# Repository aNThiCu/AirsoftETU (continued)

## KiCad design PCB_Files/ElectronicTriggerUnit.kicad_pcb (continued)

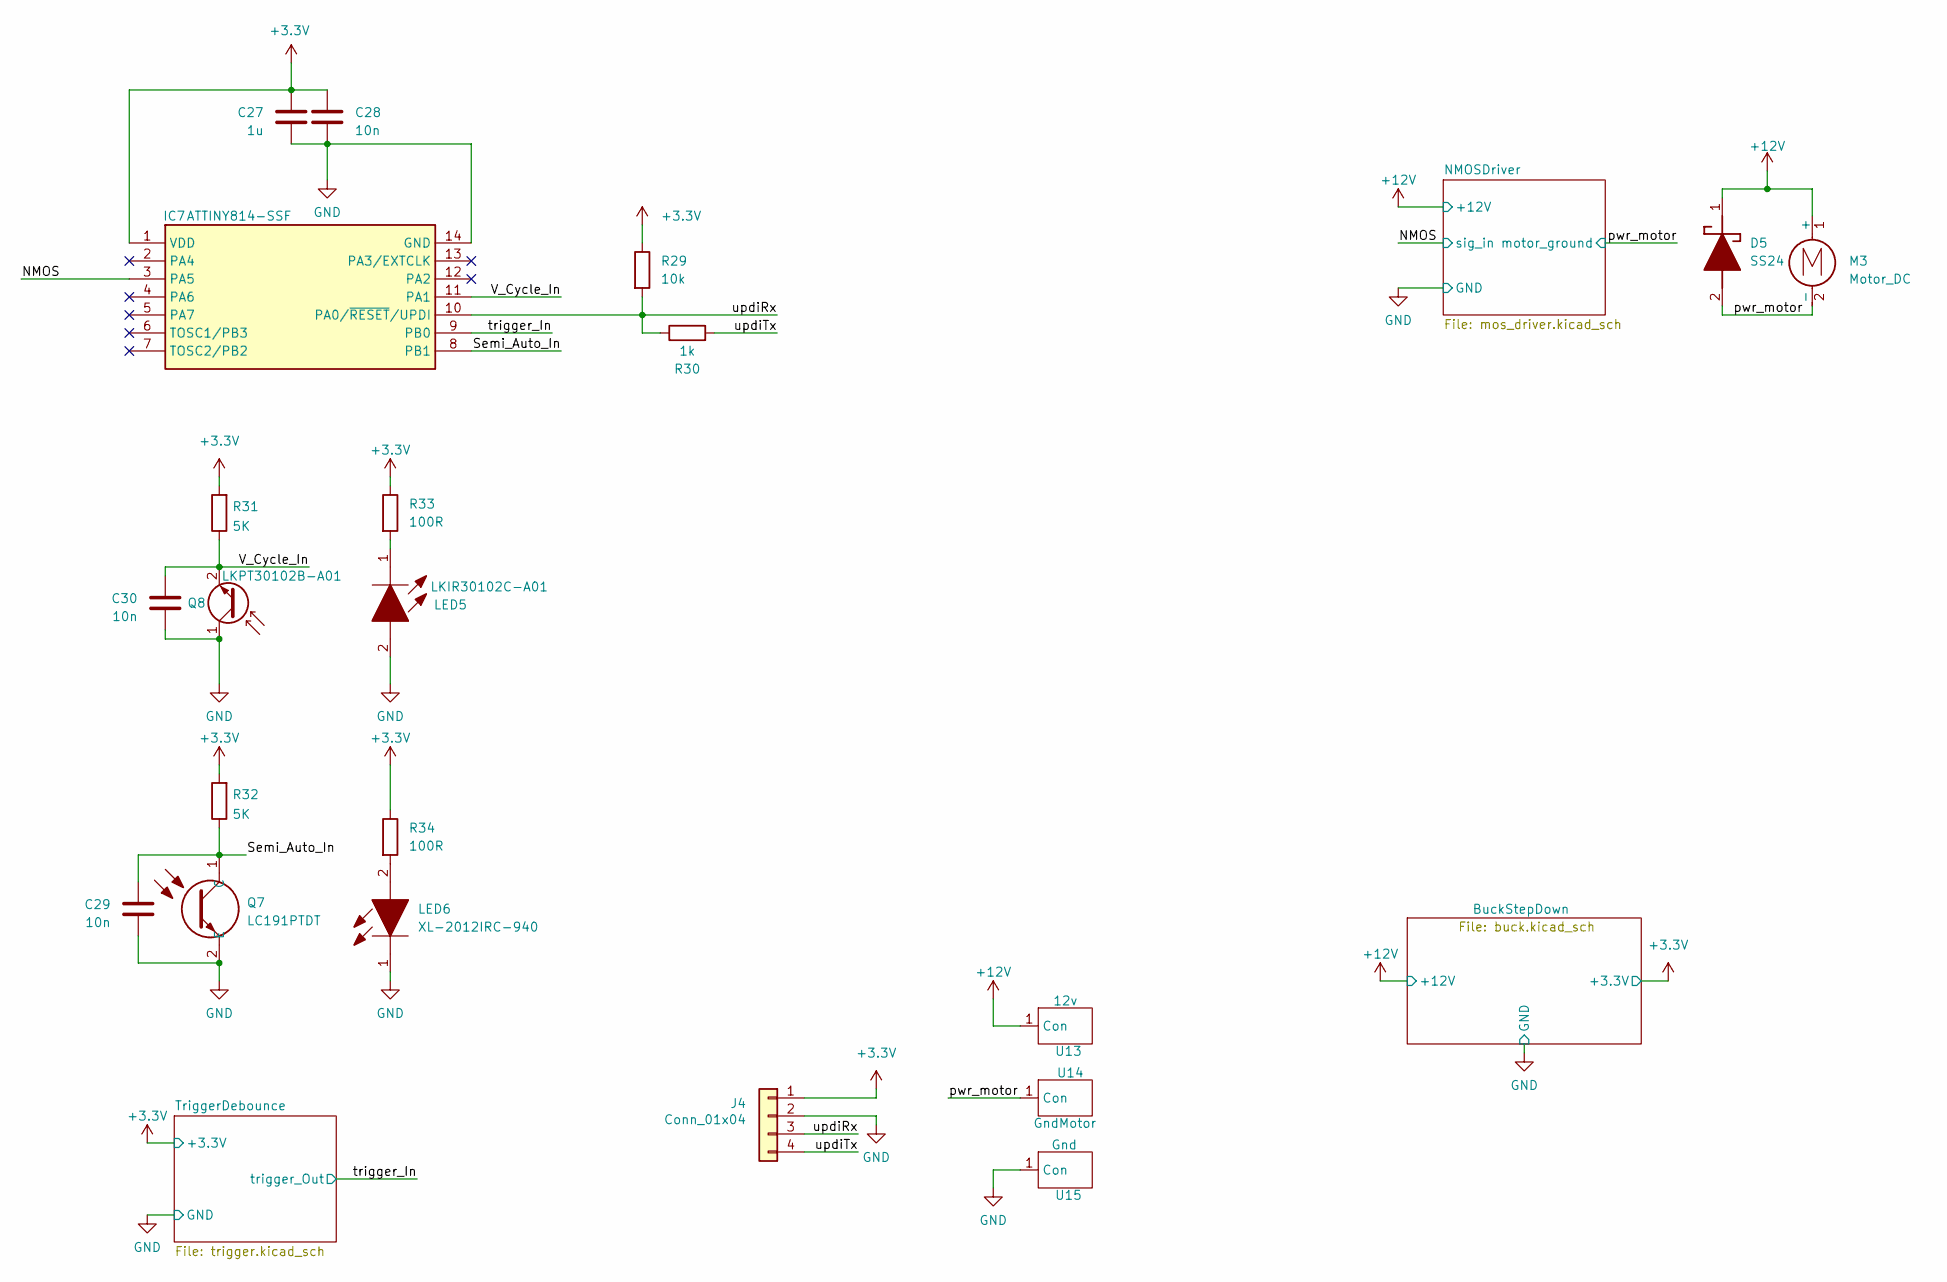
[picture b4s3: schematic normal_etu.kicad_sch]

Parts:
C27: 1u; C_0603_1608Metric
C28, C29, C30: 10n; C_0603_1608Metric
D5: SS24; DIOM5436X247N; Mouser Part Number 821-SS24
IC7: ATTINY814-SSF; SOIC127P600X175-14N; Mouser Part Number 579-ATTINY814-SSF
J4: Conn_01x04; PinHeader_1x04_P2.54mm_Vertical
LED5: LKIR30102C-A01; APA3010P3C; Mouser Part Number 755-CSL1501RW1
LED6: XL-2012IRC-940; LEDC2012X105N; Mouser Part Number 604-APTD2012SF4C
M3: Motor_DC
Q7: LC191PTDT; AP1608P1CP22; Mouser Part Number 604-AP1608P1C-P22
Q8: LKPT30102B-A01; APA3010P3C
R29: 10k; R_0603_1608Metric
R30: 1k; R_0603_1608Metric
R31, R32: 5K; R_0603_1608Metric
R33, R34: 100R; R_0603_1608Metric
U13: 12v; Copper_Pad
U14: GndMotor; Copper_Pad
U15: Gnd; Copper_Pad

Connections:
+3.3V: C27.1, C28.1, IC7.1 (VDD), J4.1, R29.1, R31.2, R32.2, R33.1, R34.1; also elsewhere on the board
+12V: D5.1 (K), M3.1 (+), U13.1 (Con); also elsewhere on the board
/NormalEtu/NMOS: IC7.3 (PA5); also elsewhere on the board
/NormalEtu/Semi_Auto_In: C29.1, IC7.8 (PB1), Q7.1 (C), R32.1
/NormalEtu/V_Cycle_In: C30.1, IC7.11 (PA1), Q8.2 (E), R31.1
/NormalEtu/pwr_motor: D5.2 (A), M3.2 (-), U14.1 (Con); also elsewhere on the board
/NormalEtu/trigger_In: IC7.9 (PB0); also elsewhere on the board
/NormalEtu/updiRx: IC7.10 (PA0/~RESET/UPDI), J4.3, R29.2, R30.1
/NormalEtu/updiTx: J4.4, R30.2
GND: C27.2, C28.2, C29.2, C30.2, IC7.14 (GND), J4.2, LED5.2, LED6.1, Q7.2 (E), Q8.1 (C), U15.1 (Con); also elsewhere on the board
unnamed: LED5.1, R33.2
unnamed: LED6.2, R34.2

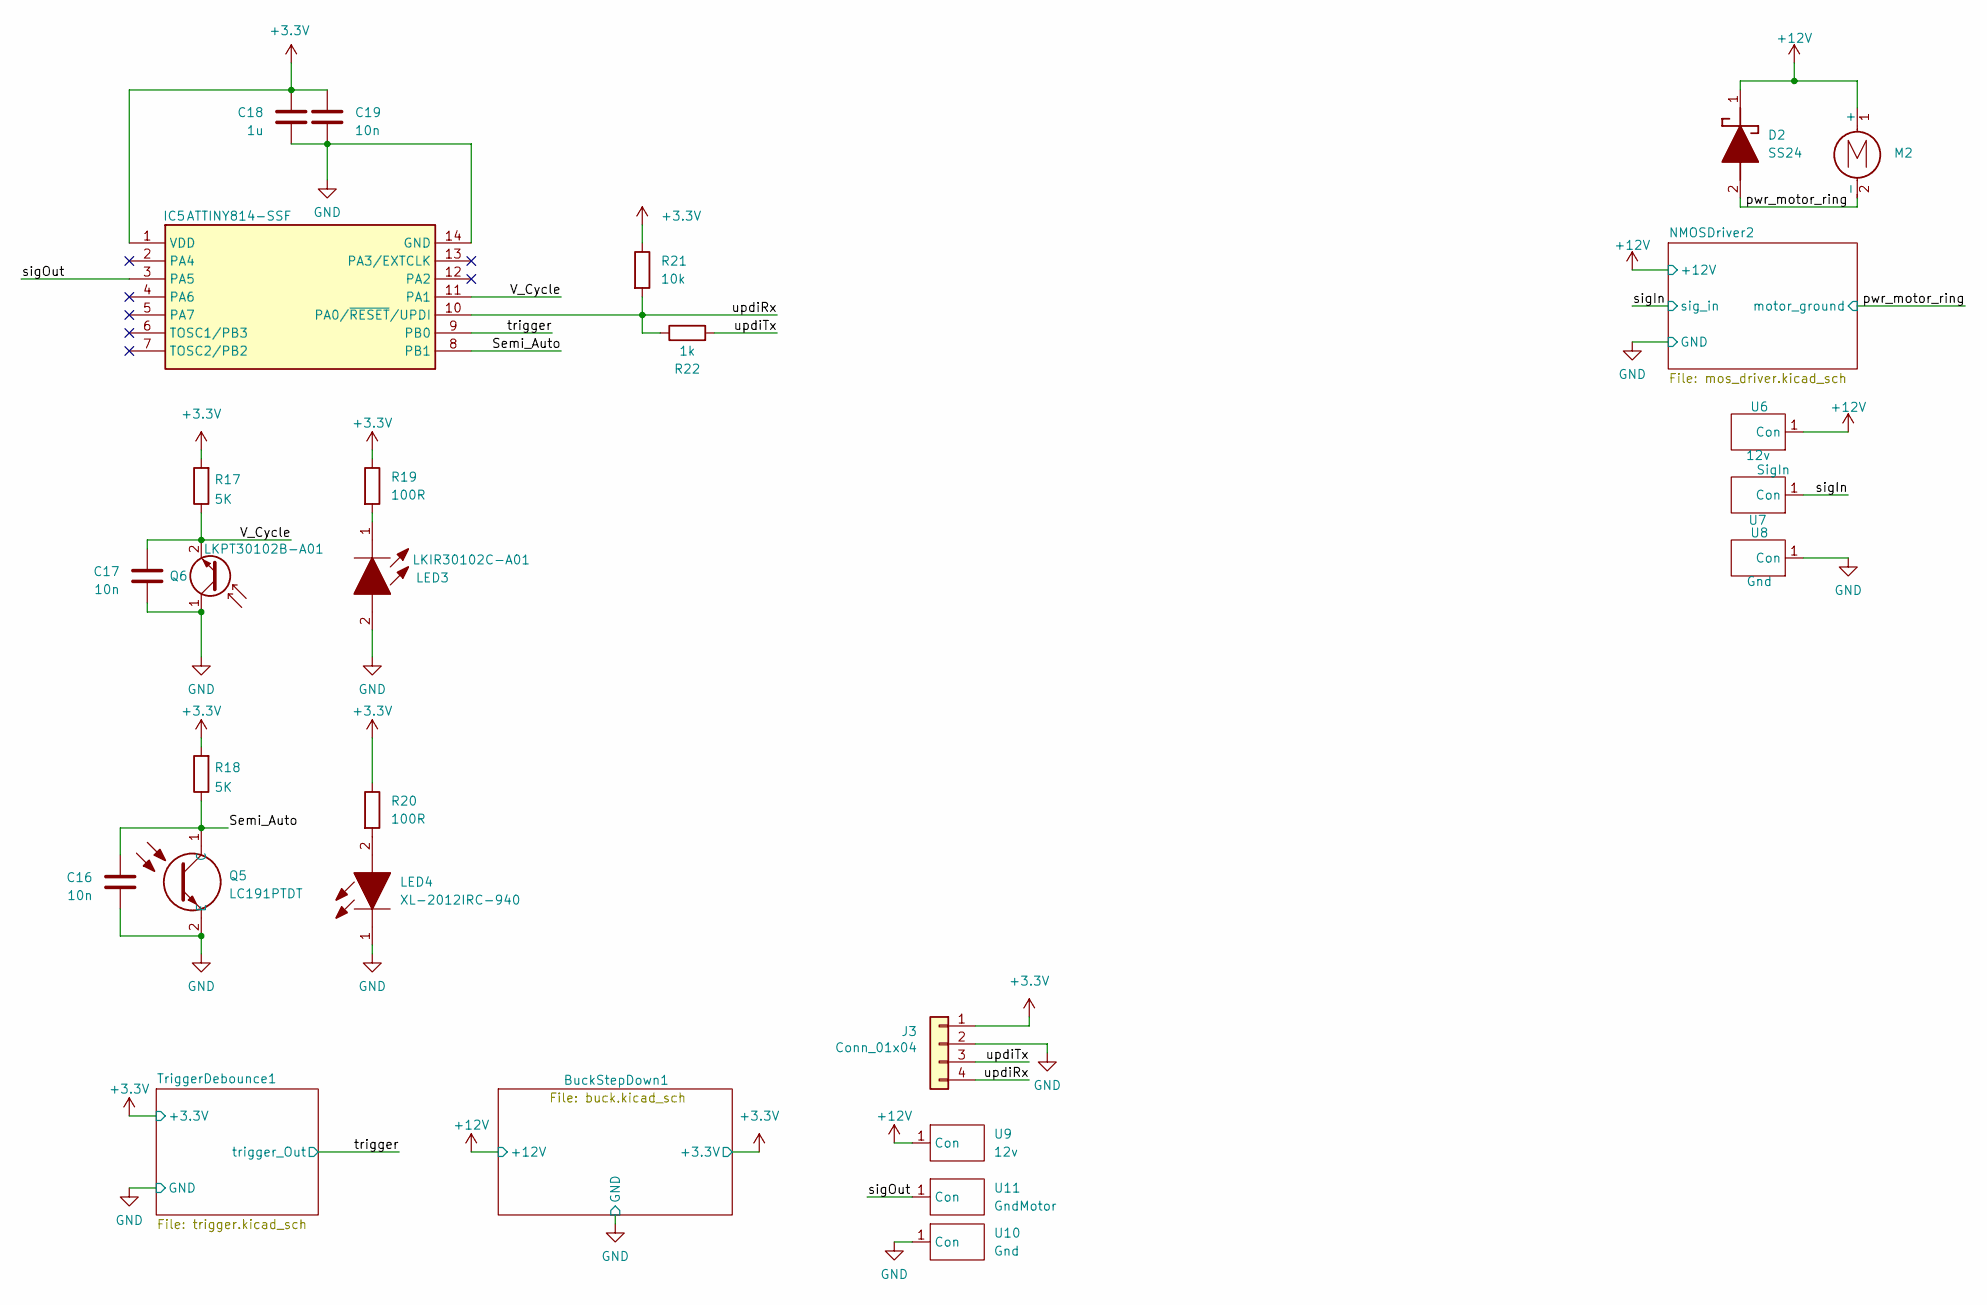
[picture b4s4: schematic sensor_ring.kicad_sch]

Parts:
C16, C17, C19: 10n; C_0603_1608Metric
C18: 1u; C_0603_1608Metric
D2: SS24; DIOM5436X247N; Mouser Part Number 821-SS24
IC5: ATTINY814-SSF; SOIC127P600X175-14N; Mouser Part Number 579-ATTINY814-SSF
J3: Conn_01x04; PinHeader_1x04_P2.54mm_Vertical
LED3: LKIR30102C-A01; APA3010P3C; Mouser Part Number 755-CSL1501RW1
LED4: XL-2012IRC-940; LEDC2012X105N; Mouser Part Number 604-APTD2012SF4C
M2: Motor_DC
Q5: LC191PTDT; AP1608P1CP22; Mouser Part Number 604-AP1608P1C-P22
Q6: LKPT30102B-A01; APA3010P3C
R17, R18: 5K; R_0603_1608Metric
R19, R20: 100R; R_0603_1608Metric
R21: 10k; R_0603_1608Metric
R22: 1k; R_0603_1608Metric
U6, U9: 12v; Copper_Pad
U7: SigIn; Copper_Pad
U8, U10: Gnd; Copper_Pad
U11: GndMotor; Copper_Pad

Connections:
+3.3V: C18.1, C19.1, IC5.1 (VDD), J3.1, R17.2, R18.2, R19.1, R20.1, R21.1; also elsewhere on the board
+12V: D2.1 (K), M2.1 (+), U6.1 (Con), U9.1 (Con); also elsewhere on the board
/SensorRingCombo/Semi_Auto: C16.1, IC5.8 (PB1), Q5.1 (C), R18.1
/SensorRingCombo/V_Cycle: C17.1, IC5.11 (PA1), Q6.2 (E), R17.1
/SensorRingCombo/pwr_motor_ring: D2.2 (A), M2.2 (-); also elsewhere on the board
/SensorRingCombo/sigIn: U7.1 (Con); also elsewhere on the board
/SensorRingCombo/sigOut: IC5.3 (PA5), U11.1 (Con)
/SensorRingCombo/trigger: IC5.9 (PB0); also elsewhere on the board
/SensorRingCombo/updiRx: IC5.10 (PA0/~RESET/UPDI), J3.4, R21.2, R22.1
/SensorRingCombo/updiTx: J3.3, R22.2
GND: C16.2, C17.2, C18.2, C19.2, IC5.14 (GND), J3.2, LED3.2, LED4.1, Q5.2 (E), Q6.1 (C), U8.1 (Con), U10.1 (Con); also elsewhere on the board
unnamed: LED3.1, R19.2
unnamed: LED4.2, R20.2

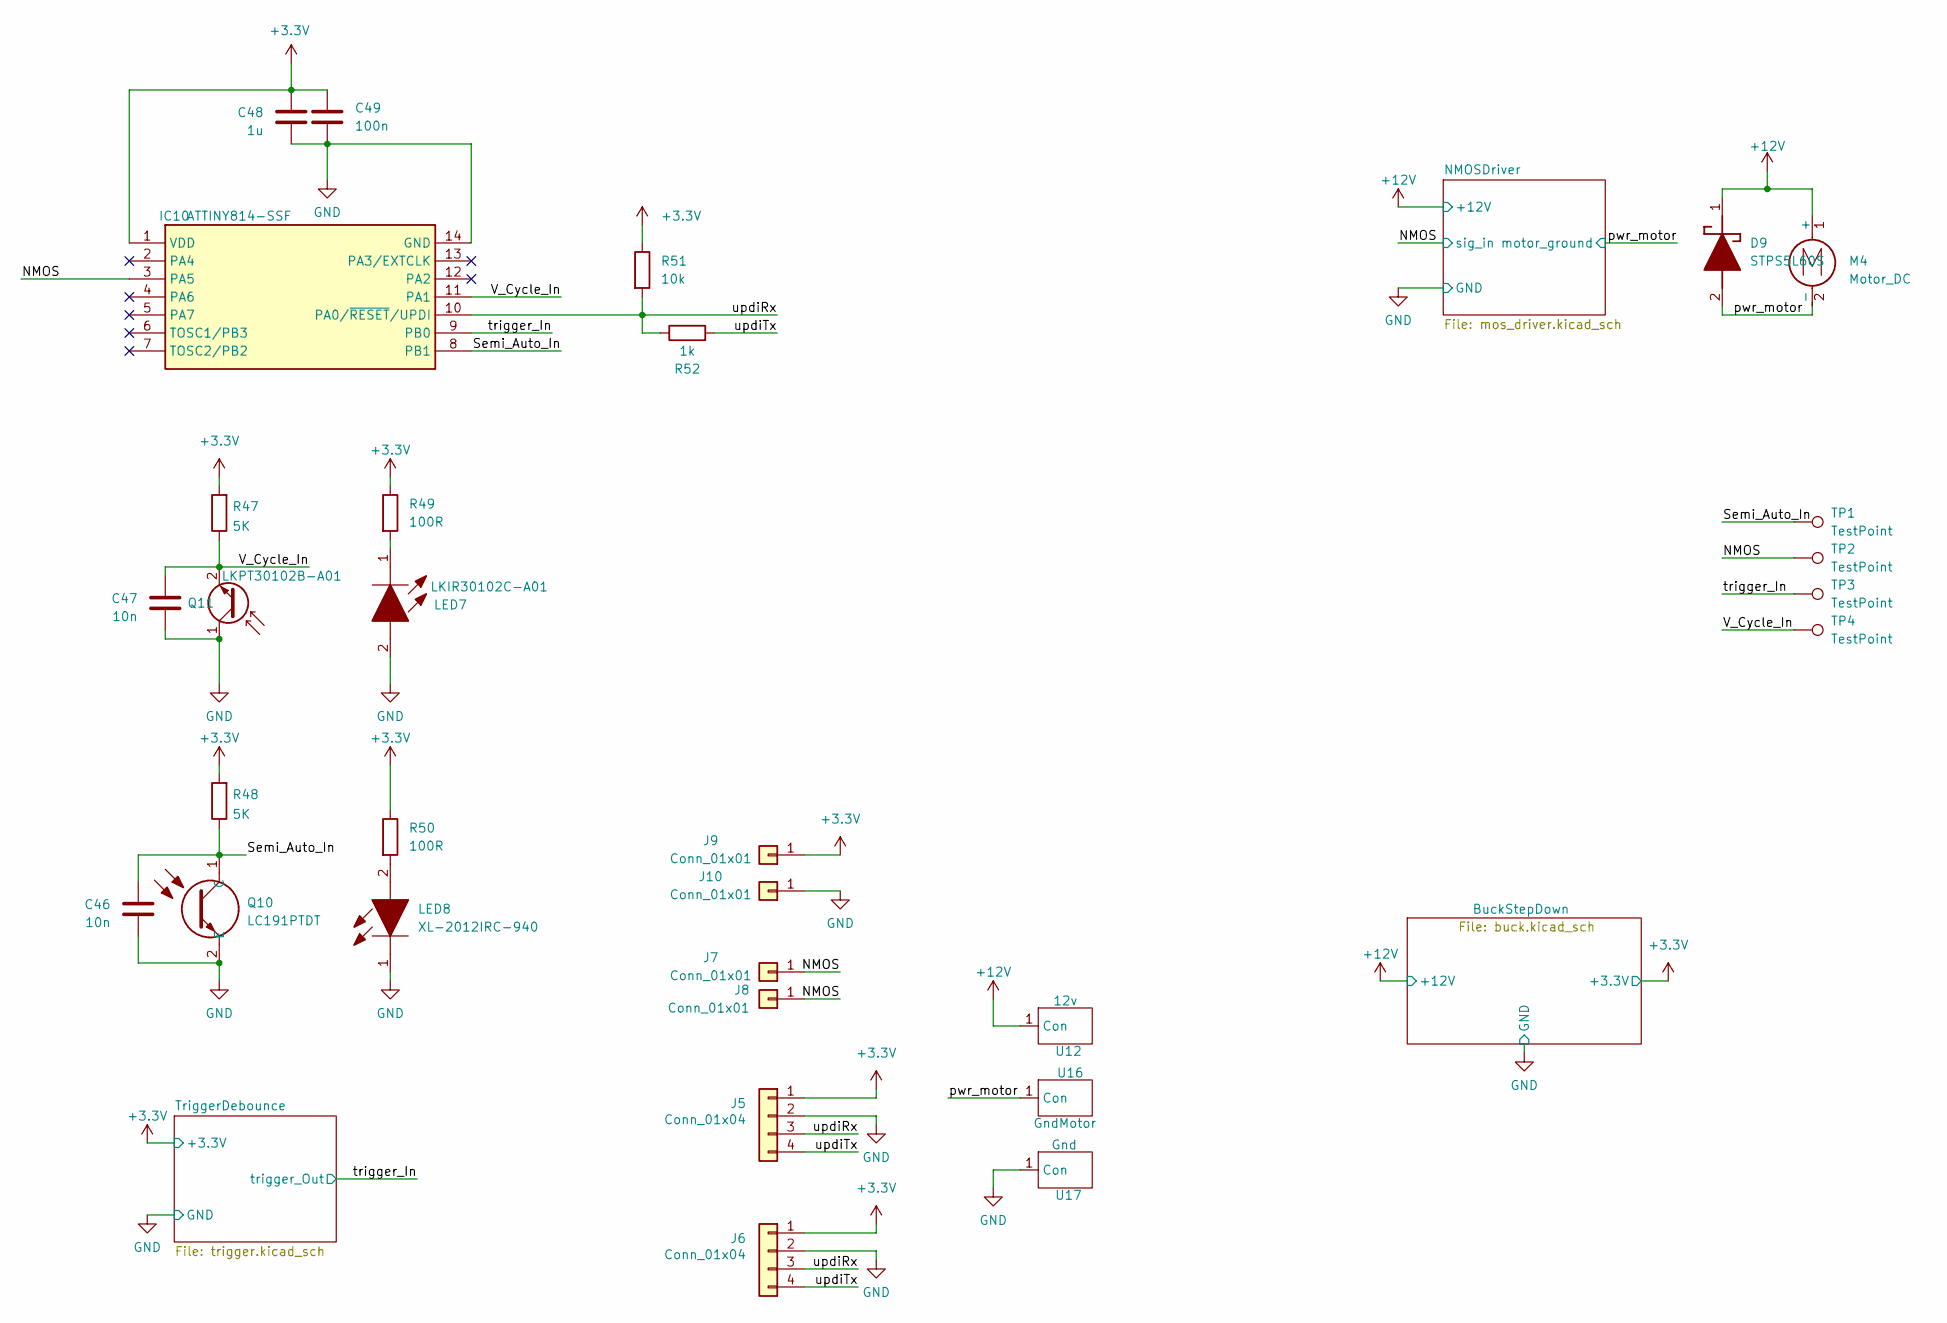
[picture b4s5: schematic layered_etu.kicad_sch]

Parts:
C46, C47: 10n; C_0603_1608Metric
C48: 1u; C_0603_1608Metric
C49: 100n; C_0603_1608Metric
D9: STPS5L60S; DIOM8059X265N; Manufacturer_Part_Number STPS5L60S
IC10: ATTINY814-SSF; SOIC127P600X175-14N; Mouser Part Number 579-ATTINY814-SSF
J5, J6: Conn_01x04; PinHeader_1x04_P2.54mm_Vertical
J7, J8, J9, J10: Conn_01x01; PinHeader_1x01_P2.54mm_Vertical
LED7: LKIR30102C-A01; APA3010P3C; Mouser Part Number 755-CSL1501RW1
LED8: XL-2012IRC-940; LEDC2012X105N; Mouser Part Number 604-APTD2012SF4C
M4: Motor_DC
Q10: LC191PTDT; AP1608P1CP22; Mouser Part Number 604-AP1608P1C-P22
Q11: LKPT30102B-A01; APA3010P3C
R47, R48: 5K; R_0603_1608Metric
R49, R50: 100R; R_0603_1608Metric
R51: 10k; R_0603_1608Metric
R52: 1k; R_0603_1608Metric
TP1, TP2, TP3, TP4: TestPoint; TestPoint_Loop_D1.80mm_Drill1.0mm_Beaded
U12: 12v; Copper_Pad
U16: GndMotor; Copper_Pad
U17: Gnd; Copper_Pad

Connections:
+3.3V: C48.1, C49.1, IC10.1 (VDD), J5.1, J6.1, J9.1, R47.2, R48.2, R49.1, R50.1, R51.1; also elsewhere on the board
+12V: D9.1 (K), M4.1 (+), U12.1 (Con); also elsewhere on the board
/LayeredEtu/NMOS: IC10.3 (PA5), J7.1, J8.1, TP2.1; also elsewhere on the board
/LayeredEtu/Semi_Auto_In: C46.1, IC10.8 (PB1), Q10.1 (C), R48.1, TP1.1
/LayeredEtu/V_Cycle_In: C47.1, IC10.11 (PA1), Q11.2 (E), R47.1, TP4.1
/LayeredEtu/pwr_motor: D9.2 (A), M4.2 (-), U16.1 (Con); also elsewhere on the board
/LayeredEtu/trigger_In: IC10.9 (PB0), TP3.1; also elsewhere on the board
/LayeredEtu/updiRx: IC10.10 (PA0/~RESET/UPDI), J5.3, J6.3, R51.2, R52.1
/LayeredEtu/updiTx: J5.4, J6.4, R52.2
GND: C46.2, C47.2, C48.2, C49.2, IC10.14 (GND), J5.2, J6.2, J10.1, LED7.2, LED8.1, Q10.2 (E), Q11.1 (C), U17.1 (Con); also elsewhere on the board
unnamed: LED7.1, R49.2
unnamed: LED8.2, R50.2

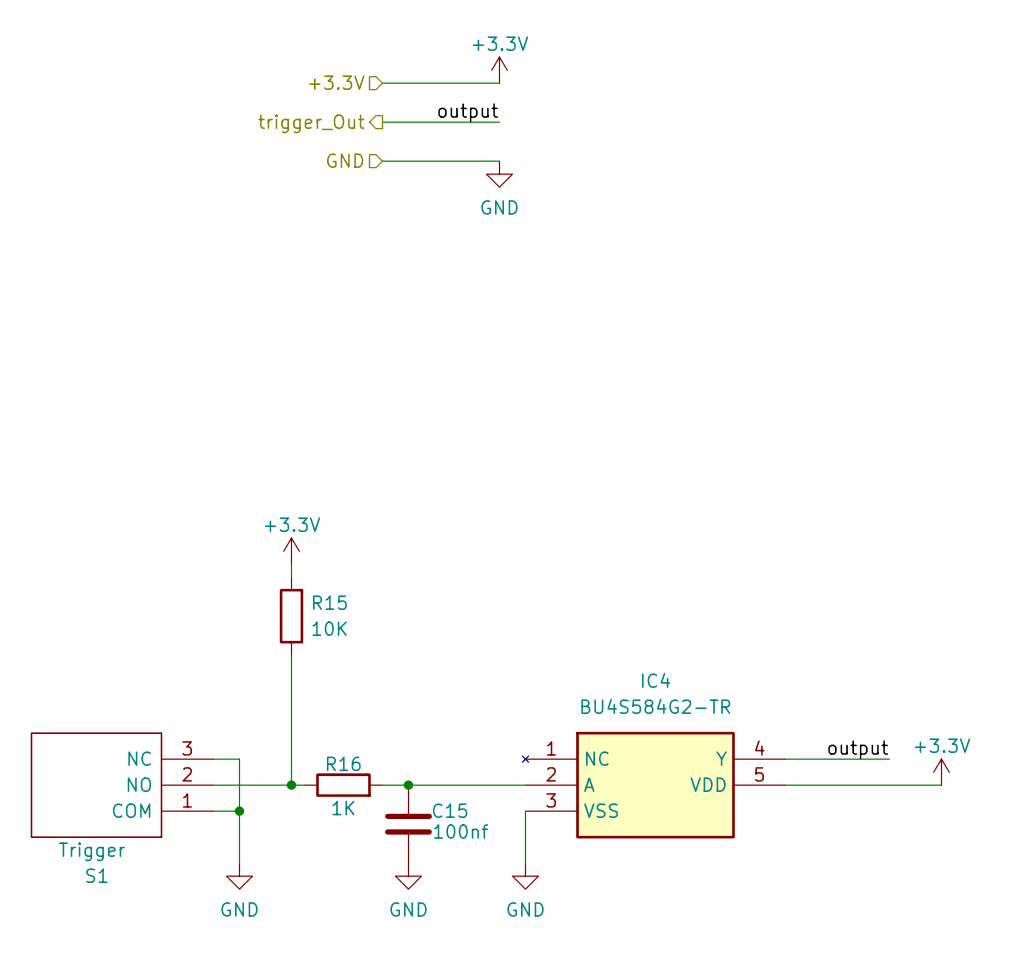
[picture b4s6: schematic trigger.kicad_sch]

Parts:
C15: 100nf; C_0603_1608Metric
IC4: BU4S584G2-TR; SOT95P280X125-5N; Mouser Part Number 755-BU4S584G2-TR
R15: 10K; R_0603_1608Metric
R16: 1K; R_0603_1608Metric
S1: Trigger; 463092691402; Mouser Part Number 710-463092691402

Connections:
+3.3V: IC4.5 (VDD), R15.2; also elsewhere on the board
/ControlSensorCombo/trigger_Out: IC4.4 (Y)
GND: C15.1, IC4.3 (VSS), S1.1 (COM), S1.3 (NC); also elsewhere on the board
unnamed: C15.2, IC4.2 (A), R16.2
unnamed: R15.1, R16.1, S1.2 (NO)

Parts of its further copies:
C26, C31, C52: 100nf; C_0603_1608Metric
IC6, IC8, IC12: BU4S584G2-TR; SOT95P280X125-5N; Mouser Part Number 755-BU4S584G2-TR
R27, R35, R55: 10K; R_0603_1608Metric
R28, R36, R56: 1K; R_0603_1608Metric
S2, S3, S4: Trigger; 463092691402; Mouser Part Number 710-463092691402

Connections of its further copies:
+3.3V: IC6.5 (VDD), IC8.5 (VDD), IC12.5 (VDD), R27.2, R35.2, R55.2; also elsewhere on the board
/LayeredEtu/trigger_In: IC12.4 (Y); also elsewhere on the board
/NormalEtu/trigger_In: IC8.4 (Y); also elsewhere on the board
/SensorRingCombo/trigger: IC6.4 (Y); also elsewhere on the board
GND: C26.1, C31.1, C52.1, IC6.3 (VSS), IC8.3 (VSS), IC12.3 (VSS), S2.1 (COM), S2.3 (NC), S3.1 (COM), S3.3 (NC), S4.1 (COM), S4.3 (NC); also elsewhere on the board
unnamed: C26.2, IC6.2 (A), R28.2
unnamed: C31.2, IC8.2 (A), R36.2
unnamed: C52.2, IC12.2 (A), R56.2
unnamed: R27.1, R28.1, S2.2 (NO)
unnamed: R35.1, R36.1, S3.2 (NO)
unnamed: R55.1, R56.1, S4.2 (NO)

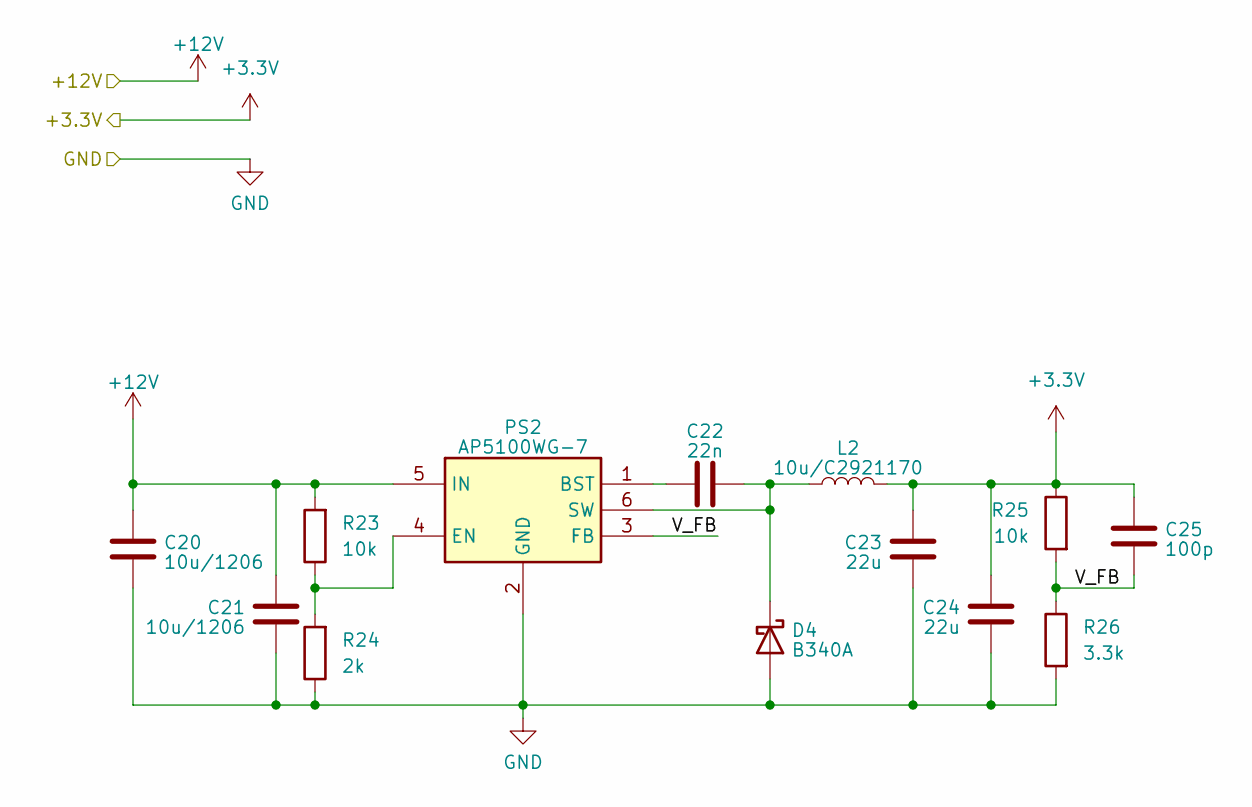
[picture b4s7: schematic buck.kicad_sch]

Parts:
C20, C21: 10u/1206; C_0603_1608Metric; MPN C13585
C22: 22n; C_0603_1608Metric; MPN C21122
C23, C24: 22u; C_0603_1608Metric; MPN C45783
C25: 100p; C_0603_1608Metric; MPN C1790
D4: B340A; D_SMA; MPN C3018525
L2: 10u/C2921170; L_Chilisin_BMRA00040420; MPN C2921170
PS2: AP5100WG-7; SOT95P285X140-6N; Mouser Part Number 621-AP5100WG-7
R23, R25: 10k; R_0603_1608Metric; MPN C25804
R24: 2k; R_0603_1608Metric; MPN C22975
R26: 3.3k; R_0603_1608Metric; MPN C22975

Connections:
+3.3V: C23.1, C24.1, C25.1, L2.2, R25.1; also elsewhere on the board
+12V: C20.1, C21.1, PS2.5 (IN), R23.2; also elsewhere on the board
/SensorRingCombo/BuckStepDown1/V_FB: C25.2, PS2.3 (FB), R25.2, R26.1
GND: C20.2, C21.2, C23.2, C24.2, D4.2 (A), PS2.2 (GND), R24.1, R26.2; also elsewhere on the board
unnamed: C22.2, D4.1 (K), L2.1, PS2.6 (SW)
unnamed: C22.1, PS2.1 (BST)
unnamed: PS2.4 (EN), R23.1, R24.2

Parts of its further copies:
C9, C10, C32, C33, C40, C41: 10u/1206; C_0603_1608Metric; MPN C13585
C11, C34, C42: 22n; C_0603_1608Metric; MPN C21122
C12, C13, C35, C36, C43, C44: 22u; C_0603_1608Metric; MPN C45783
C14, C37, C45: 100p; C_0603_1608Metric; MPN C1790
D3, D6, D7: B340A; D_SMA; MPN C3018525
L1, L3, L4: 10u/C2921170; L_Chilisin_BMRA00040420; MPN C2921170
PS1, PS3, PS4: AP5100WG-7; SOT95P285X140-6N; Mouser Part Number 621-AP5100WG-7
R11, R13, R37, R39, R43, R45: 10k; R_0603_1608Metric; MPN C25804
R12, R38, R44: 2k; R_0603_1608Metric; MPN C22975
R14, R40, R46: 3.3k; R_0603_1608Metric; MPN C22975

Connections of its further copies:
+3.3V: C12.1, C13.1, C14.1, C35.1, C36.1, C37.1, C43.1, C44.1, C45.1, L1.2, L3.2, L4.2, R13.1, R39.1, R45.1; also elsewhere on the board
+12V: C9.1, C10.1, C32.1, C33.1, C40.1, C41.1, PS1.5 (IN), PS3.5 (IN), PS4.5 (IN), R11.2, R37.2, R43.2; also elsewhere on the board
/ControlSensorCombo/BuckStepDown/V_FB: C14.2, PS1.3 (FB), R13.2, R14.1
/LayeredEtu/BuckStepDown/V_FB: C45.2, PS4.3 (FB), R45.2, R46.1
/NormalEtu/BuckStepDown/V_FB: C37.2, PS3.3 (FB), R39.2, R40.1
GND: C9.2, C10.2, C12.2, C13.2, C32.2, C33.2, C35.2, C36.2, C40.2, C41.2, C43.2, C44.2, D3.2 (A), D6.2 (A), D7.2 (A), PS1.2 (GND), PS3.2 (GND), PS4.2 (GND), R12.1, R14.2, R38.1, R40.2, R44.1, R46.2; also elsewhere on the board
unnamed: C11.2, D3.1 (K), L1.1, PS1.6 (SW)
unnamed: C34.2, D6.1 (K), L3.1, PS3.6 (SW)
unnamed: C42.2, D7.1 (K), L4.1, PS4.6 (SW)
unnamed: C11.1, PS1.1 (BST)
unnamed: PS1.4 (EN), R11.1, R12.2
unnamed: C34.1, PS3.1 (BST)
unnamed: PS3.4 (EN), R37.1, R38.2
unnamed: C42.1, PS4.1 (BST)
unnamed: PS4.4 (EN), R43.1, R44.2

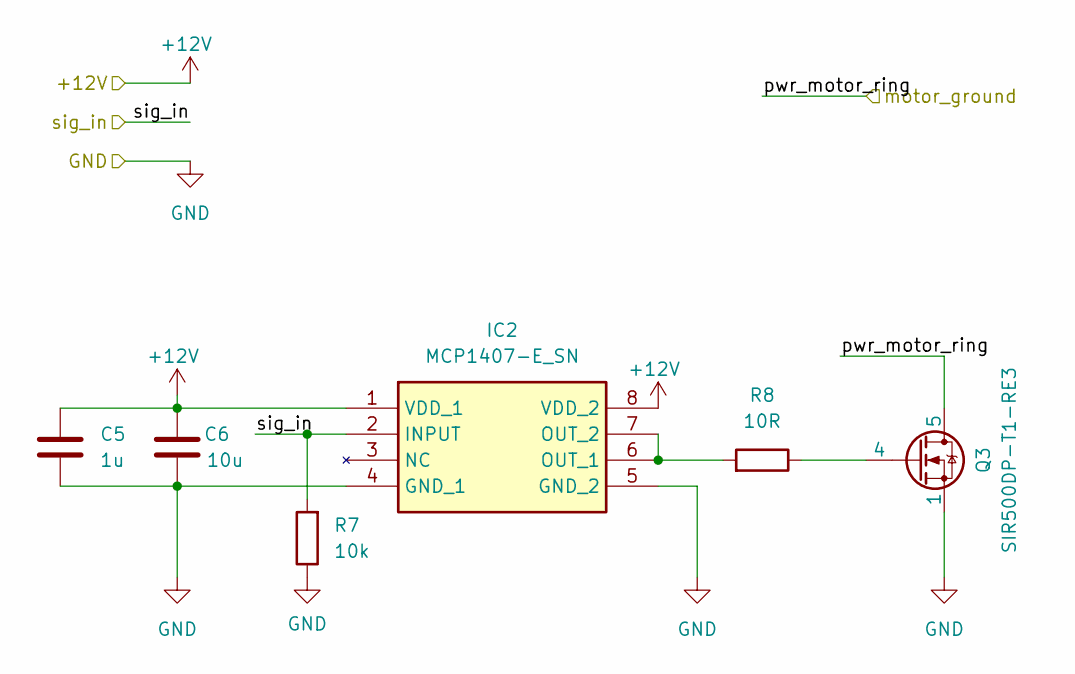
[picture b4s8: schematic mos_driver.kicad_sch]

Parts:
C5: 1u; C_0603_1608Metric
C6: 10u; C_0603_1608Metric
IC2: MCP1407-E_SN; SOIC127P600X175-8N; Mouser Part Number 579-MCP1407-E/SN
Q3: SIR500DP-T1-RE3; POWERPAKSO-8
R7: 10k; R_0603_1608Metric
R8: 10R; R_1206_3216Metric

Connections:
+12V: C5.1, C6.2, IC2.1 (VDD_1), IC2.8 (VDD_2); also elsewhere on the board
/ControlSensorCombo/NMOS: IC2.2 (INPUT), R7.2; also elsewhere on the board
/ControlSensorCombo/pwr_motor: Q3.5, Q3.6, Q3.7, Q3.8, Q3.9; also elsewhere on the board
GND: C5.2, C6.1, IC2.4 (GND_1), IC2.5 (GND_2), Q3.1, Q3.2, Q3.3, R7.1; also elsewhere on the board
unnamed: IC2.6 (OUT_1), IC2.7 (OUT_2), R8.2
unnamed: Q3.4, R8.1

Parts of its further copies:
C7, C38, C50: 1u; C_0603_1608Metric
C8, C39, C51: 10u; C_0603_1608Metric
IC3, IC9, IC11: MCP1407-E_SN; SOIC127P600X175-8N; Mouser Part Number 579-MCP1407-E/SN
Q4, Q9, Q12: SIR500DP-T1-RE3; POWERPAKSO-8
R9, R41, R53: 10k; R_0603_1608Metric
R10, R42, R54: 10R; R_1206_3216Metric

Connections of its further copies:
+12V: C7.1, C8.2, C38.1, C39.2, C50.1, C51.2, IC3.1 (VDD_1), IC3.8 (VDD_2), IC9.1 (VDD_1), IC9.8 (VDD_2), IC11.1 (VDD_1), IC11.8 (VDD_2); also elsewhere on the board
/LayeredEtu/NMOS: IC11.2 (INPUT), R53.2; also elsewhere on the board
/LayeredEtu/pwr_motor: Q12.5, Q12.6, Q12.7, Q12.8, Q12.9; also elsewhere on the board
/NormalEtu/NMOS: IC9.2 (INPUT), R41.2; also elsewhere on the board
/NormalEtu/pwr_motor: Q9.5, Q9.6, Q9.7, Q9.8, Q9.9; also elsewhere on the board
/SensorRingCombo/pwr_motor_ring: Q4.5, Q4.6, Q4.7, Q4.8, Q4.9; also elsewhere on the board
/SensorRingCombo/sigIn: IC3.2 (INPUT), R9.2; also elsewhere on the board
GND: C7.2, C8.1, C38.2, C39.1, C50.2, C51.1, IC3.4 (GND_1), IC3.5 (GND_2), IC9.4 (GND_1), IC9.5 (GND_2), IC11.4 (GND_1), IC11.5 (GND_2), Q4.1, Q4.2, Q4.3, Q9.1, Q9.2, Q9.3, Q12.1, Q12.2, Q12.3, R9.1, R41.1, R53.1; also elsewhere on the board
unnamed: IC3.6 (OUT_1), IC3.7 (OUT_2), R10.2
unnamed: IC9.6 (OUT_1), IC9.7 (OUT_2), R42.2
unnamed: IC11.6 (OUT_1), IC11.7 (OUT_2), R54.2
unnamed: Q4.4, R10.1
unnamed: Q9.4, R42.1
unnamed: Q12.4, R54.1

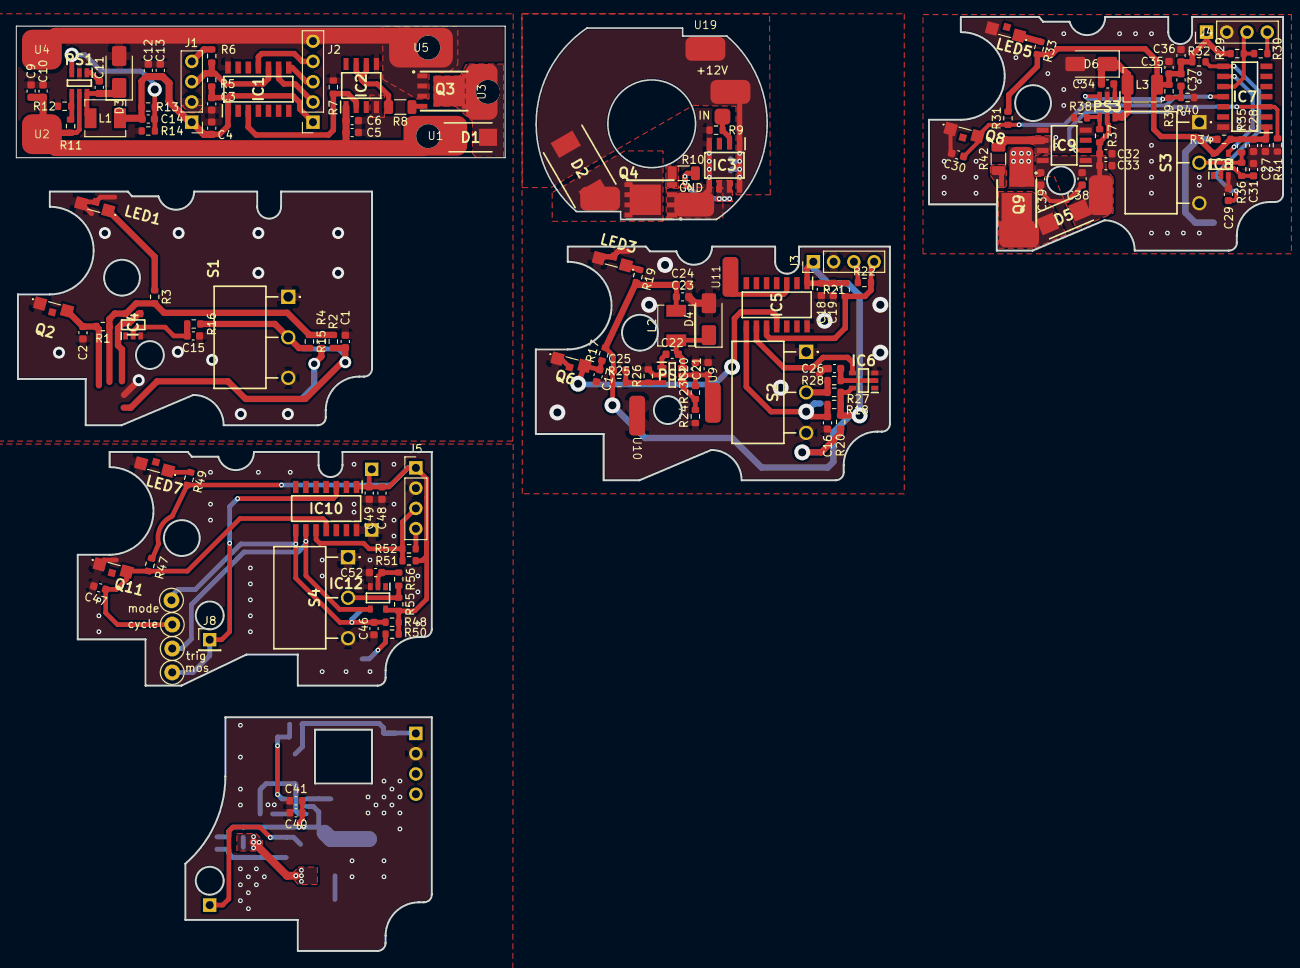
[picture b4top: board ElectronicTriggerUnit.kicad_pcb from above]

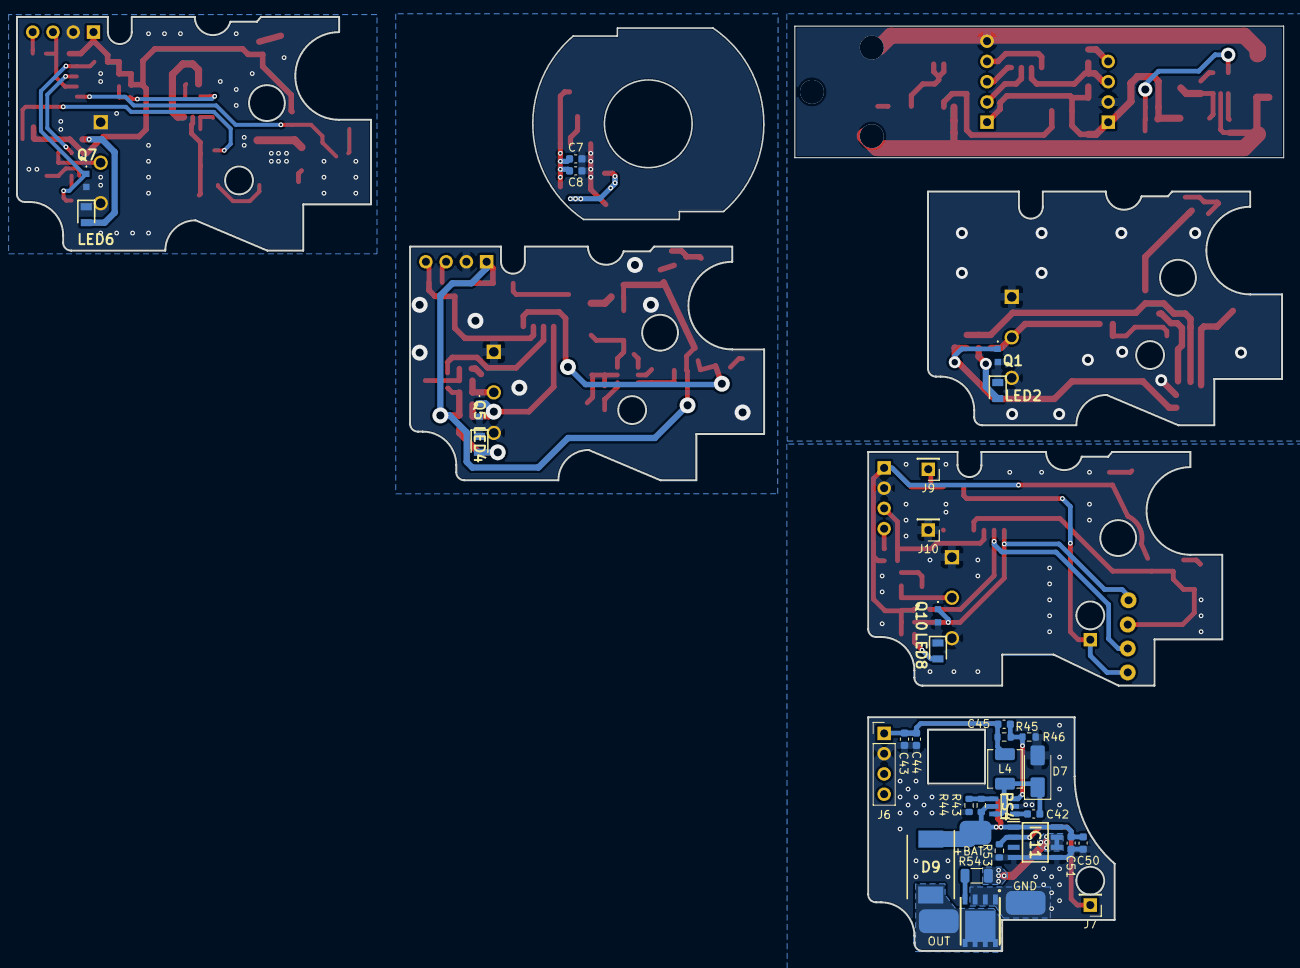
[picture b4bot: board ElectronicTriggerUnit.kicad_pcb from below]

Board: 2 copper layers, 158.8 x 117.1 mm, 193 parts (35 on the bottom side), 74 nets.

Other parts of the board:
U18: Gnd; Copper_Pad
U19: 12v; Copper_Pad

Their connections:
+12V: U19.1 (Con); also elsewhere on the board
/SensorRingCombo/pwr_motor_ring: U18.1 (Con); also elsewhere on the board

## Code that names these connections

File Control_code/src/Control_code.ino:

#include <Arduino.h>
#include <EEPROM.h>

#ifndef MOTOR_DUTY
#define MOTOR_DUTY 100
#endif

#ifndef DEAD_TIME_TICKS
#define DEAD_TIME_TICKS 2
#endif

#define DEADTIME400 __asm__ __volatile__ ("nop \n\t""nop \n\t""nop \n\t""nop \n\t""nop \n\t""nop \n\t""nop \n\t""nop \n\t")

// --- Pins ---
// FOR ATTINY814 ( in_development_ETU_AIO)
#define  TRIGGER   PIN_PB1
#define CYCLE     PIN_PA1
#define MODE      PIN_PB0
//PIN PA4 and PA5 used for output
// --- Data Structures ---

enum modeStates{
  SEMI,
  AUTO,
  BURST,
  BINARY
};

enum state{
  STANDBY,
  MOTORSTART,
  MOTORFULLPOWER,
  MOTORSTOP
};

struct selector {
  enum modeStates pos1 = SEMI;
  enum modeStates pos2 = AUTO;
};

// --- Logic Variables ---
volatile uint8_t burstCounter = 0;
bool hasBraked = true;
selector modes;
enum modeStates selectorState;
enum state motorState = STANDBY;

// --- Time Variables ---
const unsigned long motorJamTimeout = 500;
unsigned long motorJamTime = 0;
const unsigned long motorBrakeTimeout = 1000;
unsigned long motorBrakeTime = 0;

// --- TCD0 Config ---

static uint8_t TCD_PERIOD_TICKS = 156;
static uint8_t TCD_DRIVE_TICKS = ((TCD_PERIOD_TICKS * MOTOR_DUTY) / 100 >  TCD_PERIOD_TICKS - 2 * DEAD_TIME_TICKS - 2) ? TCD_PERIOD_TICKS - 2 * DEAD_TIME_TICKS - 2 : (TCD_PERIOD_TICKS * MOTOR_DUTY) / 100;
static uint8_t TCD_CMPASET_VAL = DEAD_TIME_TICKS-1;
static uint8_t TCD_CMPACLR_VAL = DEAD_TIME_TICKS +  TCD_DRIVE_TICKS-1;
static uint8_t TCD_CMPBSET_VAL = 2 * DEAD_TIME_TICKS + TCD_DRIVE_TICKS-1;
static uint8_t TCD_CMPBCLR_VAL = TCD_PERIOD_TICKS-1;


void TCD0_clear(){
  TCD0.CTRLA = 0;
  while (!(TCD0.STATUS & TCD_ENRDY_bm)) {}
  TCD0.CTRLC      = 0;
  TCD0.CTRLD      = 0;
  TCD0.CTRLE      = 0;
  TCD0.INPUTCTRLA = 0;
  TCD0.INPUTCTRLB = 0;
  TCD0.EVCTRLA    = 0;
  TCD0.EVCTRLB    = 0;
  TCD0.DLYCTRL    = 0;
}

void TCD0_init()
{    
  TCD0_clear();
  TCD0.CTRLB = TCD_WGMODE_ONERAMP_gc;
  TCD0.CMPASET = TCD_CMPASET_VAL;
  TCD0.CMPACLR = TCD_CMPACLR_VAL;
  TCD0.CMPBSET = TCD_CMPBSET_VAL;
  TCD0.CMPBCLR = TCD_CMPBCLR_VAL;
  _PROTECTED_WRITE(TCD0.FAULTCTRL, 0);

  TCD0.CTRLA = TCD_CLKSEL_SYSCLK_gc | TCD_SYNCPRES_DIV1_gc | TCD_CNTPRES_DIV4_gc;
}

void PORT_init()
{
  PORTMUX.CTRLC = 0;
  PORTA.OUTCLR = PIN4_bm | PIN5_bm;
  PORTA.PIN5CTRL |= PORT_INVEN_bm;
  PORTA.DIRSET = PIN4_bm | PIN5_bm;

}

void change_settings(){

}

void setup() {
    // Input Init
  pinMode(TRIGGER, INPUT);
  pinMode(CYCLE, INPUT);
  pinMode(MODE, INPUT);

  if (digitalRead(TRIGGER)==HIGH) change_settings(); //implement settings

  // Output Init
  PORT_init();
  if(MOTOR_DUTY < 90) TCD0_init();


  // Selector init
  // Temp comment for debugging
  // mode_change();
  selectorState = SEMI;

  // Interrupts init
  attachInterrupt(digitalPinToInterrupt(TRIGGER),  trigger_pressed, RISING);
  attachInterrupt(digitalPinToInterrupt(CYCLE), cycle_completed, RISING);
  // Temp comment for debugging
  // attachInterrupt(digitalPinToInterrupt(MODE), mode_change, CHANGE);
}

void  trigger_pressed() {
  if (motorState == STANDBY) {
    burstCounter = 0;
    motorState = MOTORSTART;
  }
}

void cycle_completed() {
  if (motorState == MOTORFULLPOWER) {
    if (selectorState == BURST) burstCounter++;
    motorJamTime = millis();
    motorState = MOTORSTOP;
  }
}

void mode_change() {
  if (digitalRead(MODE) == HIGH) {
    selectorState = modes.pos2;
  } else {
    selectorState = modes.pos1;
  }
}

void motor_on() {
  PORTA.OUTCLR = PIN4_bm | PIN5_bm;
  
  DEADTIME400;

  if(MOTOR_DUTY<90){
    _PROTECTED_WRITE(TCD0.FAULTCTRL, TCD_CMPAEN_bm | TCD_CMPBEN_bm);
    while (!(TCD0.STATUS & TCD_ENRDY_bm)) {}
    TCD0.CTRLA |= TCD_ENABLE_bm;
  } else PORTA.OUTSET = PIN4_bm;

  motorState = MOTORFULLPOWER;
  motorJamTime = millis();
}

void motor_off(){
  PORTA.OUTCLR = (PIN4_bm | PIN5_bm);

  if(MOTOR_DUTY < 90){
    while (!(TCD0.STATUS & TCD_ENRDY_bm)) {}
    TCD0.CTRLA &= ~TCD_ENABLE_bm;
    while (!(TCD0.STATUS & TCD_ENRDY_bm)) {}
    _PROTECTED_WRITE(TCD0.FAULTCTRL, 0);
  }

  DEADTIME400;
  
  PORTA.OUTCLR = PIN4_bm;
  PORTA.OUTSET = PIN5_bm;
  //add delay till break stop
  motorBrakeTime = millis();
  hasBraked = false;
  motorState = STANDBY;
}

void modes_decision(){
  motorState = MOTORFULLPOWER;
  switch (selectorState){
    case SEMI:
      motor_off();
    break;
    case AUTO:
      if(digitalRead( TRIGGER) == HIGH) motor_off();
    break;
    case BURST:
      if(digitalRead( TRIGGER) == HIGH) motor_off();
      else if(burstCounter >= 3) motor_off();
    break;
  }
}

void loop() {
  if (motorState == MOTORSTART) motor_on();
  else if (motorState == MOTORSTOP) modes_decision();

  if(!hasBraked && millis()-motorBrakeTime > motorBrakeTimeout){
   //Clear high side mos after 1 second
   PORTA.OUTCLR = PIN5_bm;
   hasBraked=true;
  }

  // Disabled for debugging purposes
  // if (motorState == MOTORFULLPOWER && (millis() - motorJamTime > motorJamTimeout)) {
  //  // The motor has been running for too long, indicating a jam
  //  motor_off();
  //  while(true){;} //Power cycle required to shoot again
  // }
}

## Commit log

2025-04-30 Fixes
2025-05-07 changed some parts
2025-05-09 redid ground plane and trace spacing
2025-05-12 added motor ring
2025-05-14 outputs of gate driver needed to be shorted :(
2025-05-20 updated code , modified resistors
2025-05-21 added a different combo
2025-05-23 small fixes for new combo
2025-09-04 moved to platformio
2025-09-04 added settings , burst mode , and basic failsafe.
2026-01-12 stacked version
2026-02-08 Parting off each design into a project
2026-04-28 more boards for testing
2026-05-13 Long list , check readme
2026-05-13 READ ME
